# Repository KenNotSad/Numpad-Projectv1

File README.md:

# Numpad-Projectv1

This project is an RP2040-powered gasket-mount numpad with a rotary encoder and OLED display, intended to help me learn introductory PCB design and QMK firmware. 

## Mechanical

The top case, bottom case, and plate were designed in SolidWorks and 3D-printed. 

## Electrical

Schematic and PCB were designed in KiCad and sent to be manufactured by JLCPCB. NOTE: The KiCad files rely on the ScottoKeebs KiCad Library. 

## Assembly

1. Solder RP2040 Zero, 1N4148 diodes, MX hotswap sockets, EC11 rotary encoder, 128X32 OLED display onto PCB
2. Add 3 2U screw-in stabilizers (1.6mm) to the PCB
3. Attach plate to PCB using 3mm standoffs and M2 x 3mm screws
4. Insert 17 MX switches into the assembly
5. Add 8 (4 on top case, 4 on bottom case) 3mm x 25mm x 1.5mm gaskets to the cases
6. Sandwich the plate between the top and bottom cases, and assemble using 4 M3 x 12mm screws
7. Add rubber feet (or tack) to the bottom case
8. Add keycaps and knob

Done!

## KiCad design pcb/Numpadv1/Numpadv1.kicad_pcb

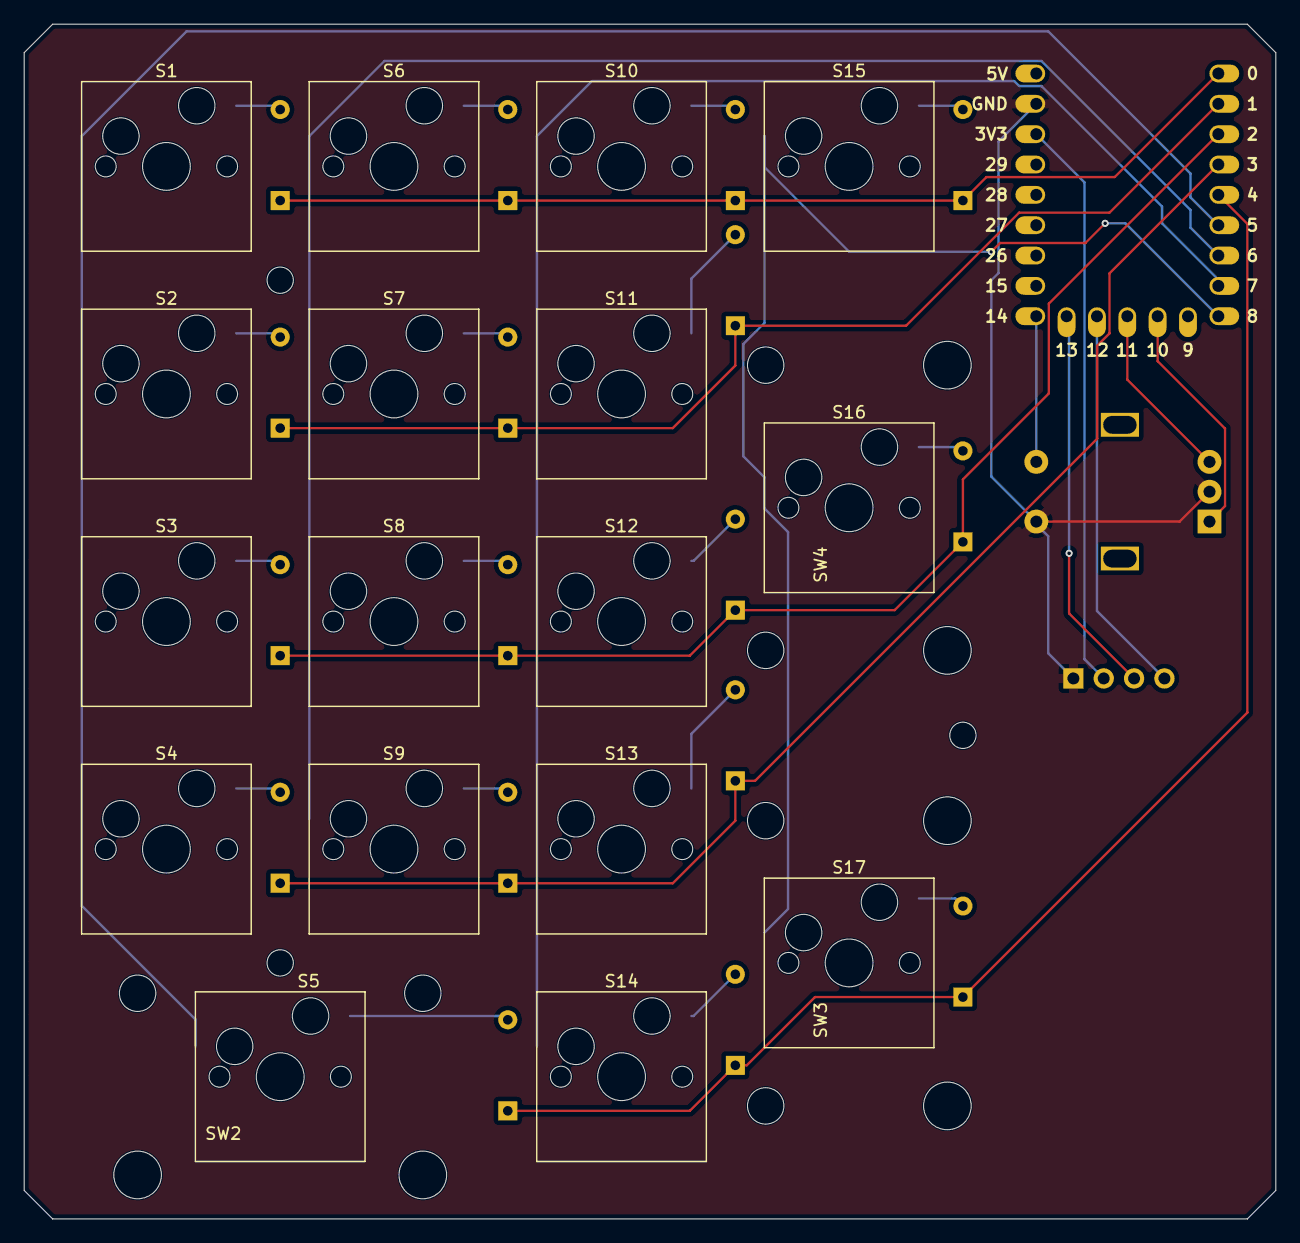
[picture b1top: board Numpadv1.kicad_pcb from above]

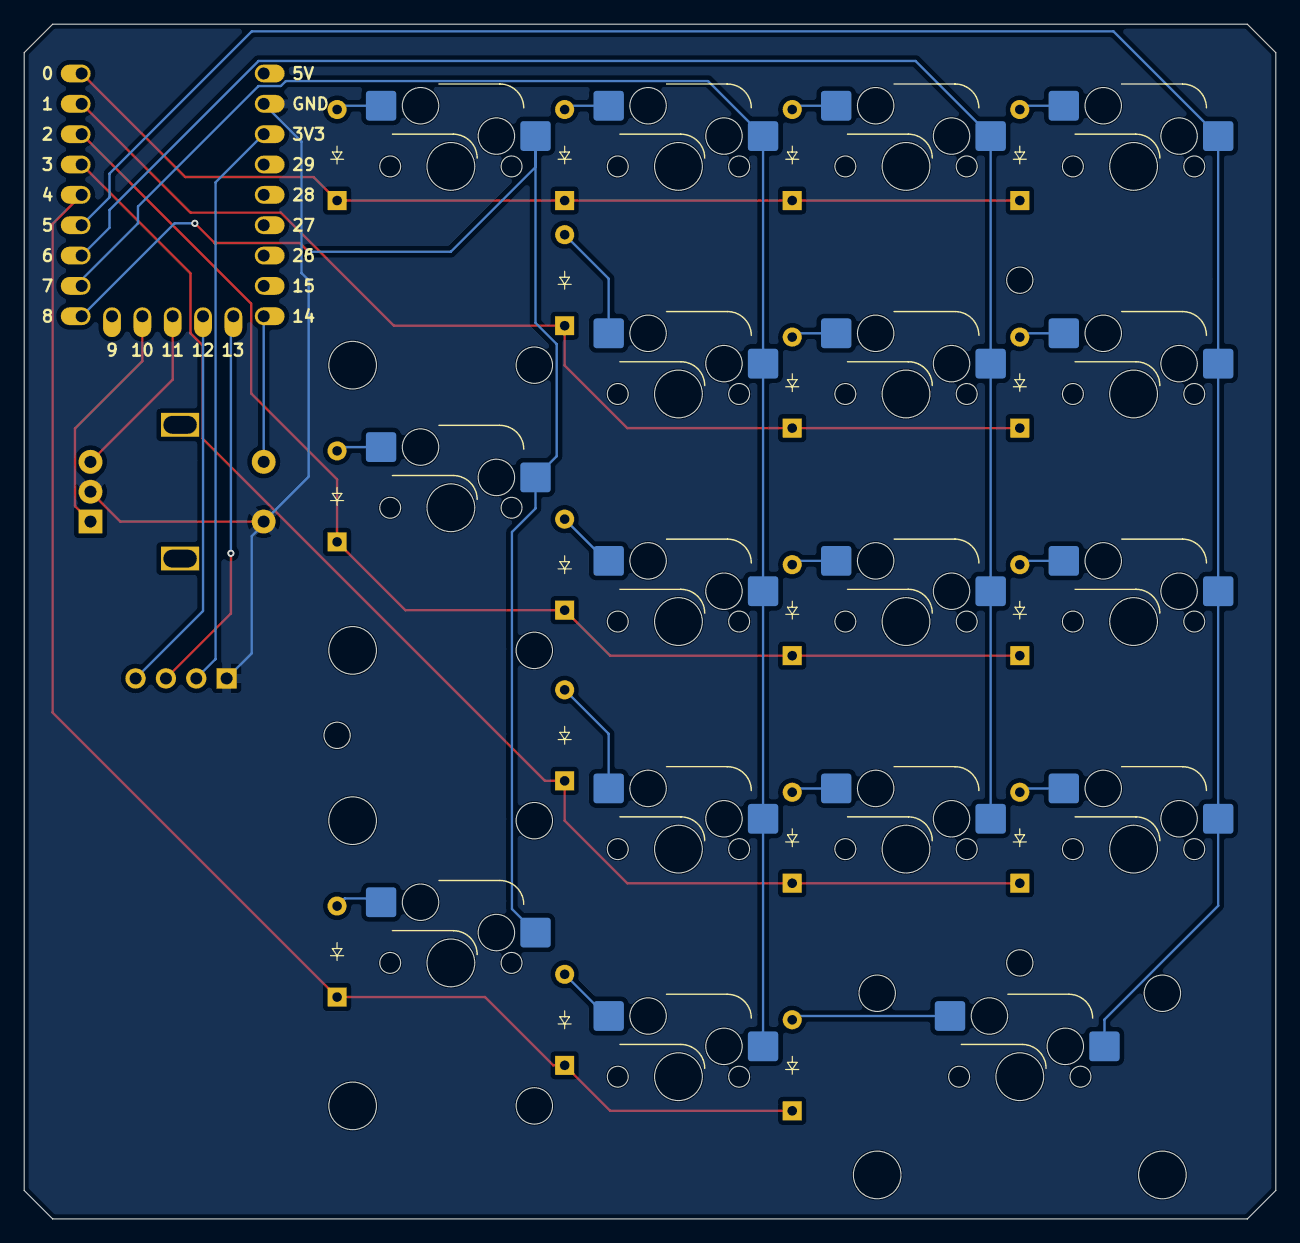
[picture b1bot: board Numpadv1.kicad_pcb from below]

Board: 2 copper layers, 104.8 x 100.0 mm, 44 parts (20 on the bottom side), 33 nets.

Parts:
D1, D2, D3, D4, D5, D6, D7, D8, D9, D10, D11, D12, D13, D14, D15, D16, D17: Diode_DO-35
H1, H2, H3, H4: Standoff_M2x4mm
J1: OLED_128x32
S1, S2, S3, S4, S6, S7, S8, S9, S10, S11, S12, S13, S14, S15: Hotswap_MX_1.00u
S5: Hotswap_MX_2.00u
S16, S17: Hotswap_MX_2.00u_90deg
SW1: RotaryEncoder_Switch; Encoder_EC11_MX
SW2, SW3, SW4: Switch; Stabilizer_MX_2.00u
U1: RP2040_Zero

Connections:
/3V3: J1.2 (VCC), U1.21 (3V3)
/Col 0: S1.1, S2.1, S3.1, S4.1, S5.1, U1.6 (5)
/Col 1: S6.1, S7.1, S8.1, S9.1, U1.7 (6)
/Col 2: S10.1, S11.1, S12.1, S13.1, S14.1, U1.8 (7)
/Col 3: S15.1, S16.1, S17.1, U1.9 (8)
/GND: J1.1 (GND), SW1.C, SW1.S2, U1.22 (GND)
/GP10: SW1.A, U1.11 (10)
/GP11: SW1.B, U1.12 (11)
/GP14: SW1.S1, U1.15 (14)
/I2C0 SCL: J1.3 (SCL), U1.14 (13)
/I2C0 SDA: J1.4 (SDA), U1.13 (12)
/Row 0: D1.1 (K), D6.1 (K), D10.1 (K), D15.1 (K), U1.1 (0)
/Row 1: D2.1 (K), D7.1 (K), D11.1 (K), U1.2 (1)
/Row 2: D3.1 (K), D8.1 (K), D12.1 (K), D16.1 (K), U1.3 (2)
/Row 3: D4.1 (K), D9.1 (K), D13.1 (K), U1.4 (3)
/Row 4: D5.1 (K), D14.1 (K), D17.1 (K), U1.5 (4)
unnamed: D1.2 (A), S1.2
unnamed: D2.2 (A), S2.2
unnamed: D3.2 (A), S3.2
unnamed: D4.2 (A), S4.2
unnamed: D5.2 (A), S5.2
unnamed: D6.2 (A), S6.2
unnamed: D7.2 (A), S7.2
unnamed: D8.2 (A), S8.2
unnamed: D9.2 (A), S9.2
unnamed: D10.2 (A), S10.2
unnamed: D11.2 (A), S11.2
unnamed: D12.2 (A), S12.2
unnamed: D13.2 (A), S13.2
unnamed: D14.2 (A), S14.2
unnamed: D15.2 (A), S15.2
unnamed: D16.2 (A), S16.2
unnamed: D17.2 (A), S17.2

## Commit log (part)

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2026-04-25 Initialize Folders
2026-04-25 Update TODO
2026-05-01 Schematics + PCB
2026-05-01 PCB UPDATED
2026-05-02 ignore
2026-05-02 Clean
2026-05-02 Clean2
2026-05-07 PCB Completed (for now)
2026-05-14 Filled Zones
2026-06-09 External Cad Files
2026-06-09 CAD Complete
2026-06-09 3D Printed Files
2026-06-09 Firmware Complete
2026-06-09 PCB Manufacturing Files
2026-06-15 Updated Screenshots
2026-06-15 Update README.md
    Added images
2026-06-20 Images Updated
2026-06-20 README.md Upated
2026-06-20 Updated README.md
    Added note about reliance on ScottoKeebs KiCad Library.
